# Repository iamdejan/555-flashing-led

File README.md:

# 555 Flashing LED

This project is my attempt on using ICM7555 timer IC from Intersil (now Renesas).

## Components

- [Intersil ICM7555 timer IC](https://www.tokopedia.com/eltech-online/icm7555-icm-7555-555-general-purpose-timer)
    - Datasheet:
        - [Renesas](https://www.renesas.com/us/en/document/dst/icm7555-icm7556-datasheet)
- Resistors:
    - R1: [33k ohm](https://www.tokopedia.com/rajaavr/10pcs-resistor-1-4w-5k6-6k8-8k2-10k-12k-15k-18k-20k-22k-27k-33k-ohm-33k-ohm)
    - R2: [120k ohm](https://www.tokopedia.com/elantech/resistor-yageo-120k-1-4w-1-0-25w-1-4-w-120-kilo-ohm-elantech)
- Capacitors:
    - [2.2 μF](www.tokopedia.com/starlectric/kapasitor-elco-capasitor-2-2-uf-2-2uf-50v)
- [Red LED 5mm](https://www.tokopedia.com/starlectric/led-5mm-merah-5pcs-pack)
- Battery:
    - [CR2032 3V battery](https://www.tokopedia.com/v-king/baterai-energizer-cr2032-bp2)
    - [CR2032 battery holder](https://www.tokopedia.com/cncstorebandung/cnc-socket-soket-tempat-holder-case-battery-baterai-kancing-cr2032)

## References

- [555 Flashing LED](https://www.555-timer-circuits.com/flashing-led.html)
- [555 timer basics - Astable mode](https://www.circuitbasics.com/555-timer-basics-astable-mode/)
- [Simple Flashing LED using 555 Timer IC](https://circuitdigest.com/electronic-circuits/flashing-led-using-555-timer-ic)
- [555 Timer Tutorial and Circuits](https://www.build-electronic-circuits.com/555-timer/)
- [555 timer calculator](https://www.digikey.com/en/resources/conversion-calculators/conversion-calculator-555-timer)
- [KiCad tutorial by Shawn Hymel](https://www.youtube.com/playlist?list=PL3bNyZYHcRSUhUXUt51W6nKvxx2ORvUQB)
- [What is the difference between VCC, VDD, VEE, and VSS](https://electronics.stackexchange.com/questions/17382/what-is-the-difference-between-v-cc-v-dd-v-ee-v-ss)

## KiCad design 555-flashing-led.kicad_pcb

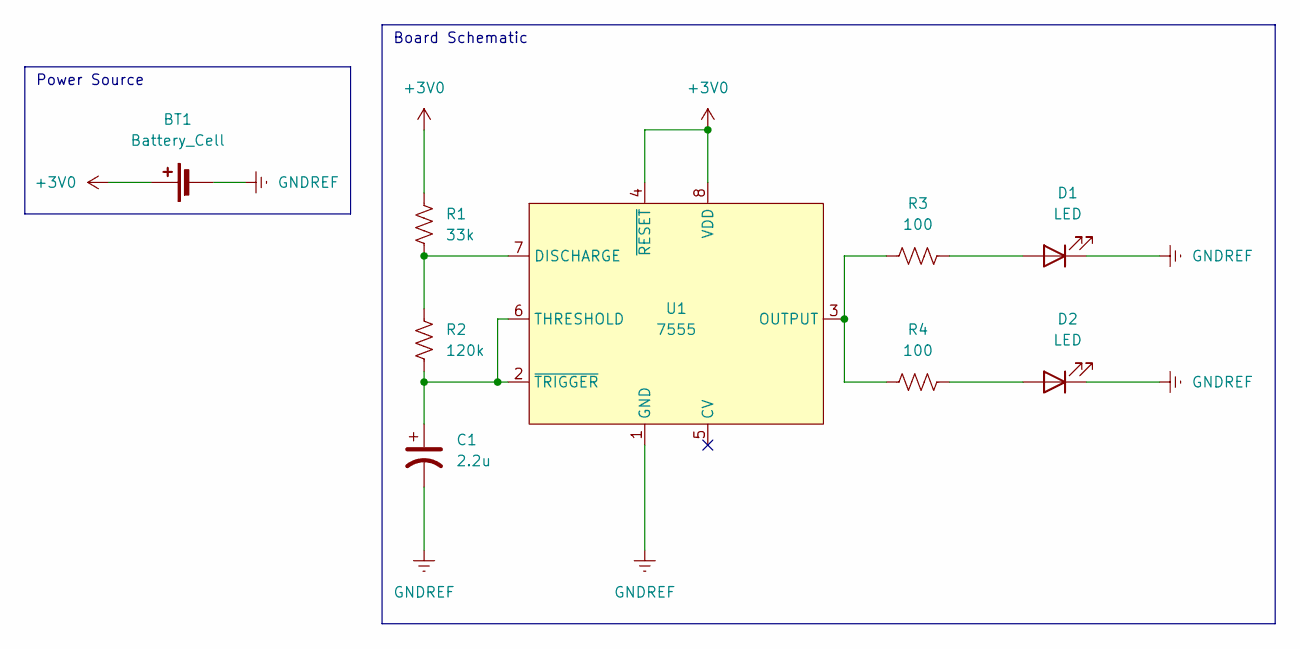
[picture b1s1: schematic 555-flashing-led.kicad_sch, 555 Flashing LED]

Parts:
BT1: Battery_Cell; BatteryHolder_Keystone_107_1x23mm
C1: 2.2u; CP_Radial_D5.0mm_P2.50mm
D1, D2: LED; LED_D5.0mm
R1: 33k; R_Axial_DIN0309_L9.0mm_D3.2mm_P15.24mm_Horizontal
R2: 120k; R_Axial_DIN0309_L9.0mm_D3.2mm_P15.24mm_Horizontal
R3, R4: 100; R_Axial_DIN0309_L9.0mm_D3.2mm_P15.24mm_Horizontal
U1: 7555; DIP-8_W7.62mm_LongPads

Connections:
+3V0: BT1.1 (+), R1.2, U1.4 (~RESET), U1.8 (VDD)
GNDREF: BT1.2 (-), C1.2, D1.1 (K), D2.1 (K), U1.1 (GND)
unnamed: D1.2 (A), R3.2
unnamed: D2.2 (A), R4.2
unnamed: R1.1, R2.1, U1.7 (DISCHARGE)
unnamed: R3.1, R4.1, U1.3 (OUTPUT)
unnamed: C1.1, R2.2, U1.2 (~TRIGGER), U1.6 (THRESHOLD)

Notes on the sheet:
Board Schematic
Power Source

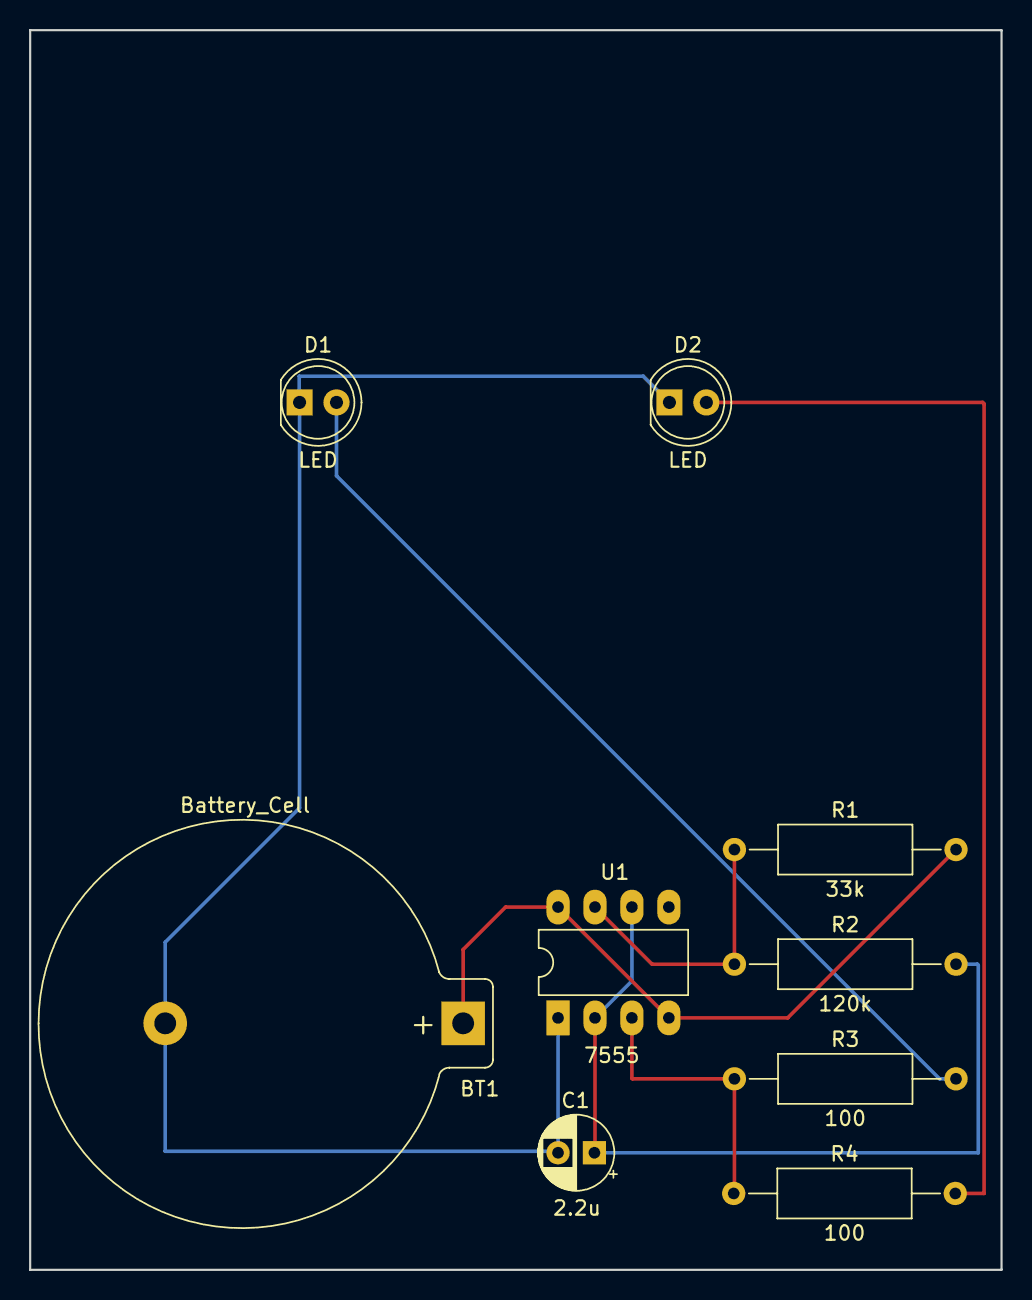
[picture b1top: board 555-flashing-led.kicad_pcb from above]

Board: 2 copper layers, 66.8 x 85.3 mm, 9 parts (0 on the bottom side), 7 nets.

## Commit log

2023-08-13 create custom symbol for 7555 timer; add README
2023-08-13 add license
2023-08-13 add kicad tutorial to references
2023-08-13 create schematic diagram; add reference in README
2023-08-18 Add reference
2023-08-20 use footprint from library
2023-08-26 finalize pcb
2023-08-26 arrange PCB component (#1)
2023-09-03 update capacitors
